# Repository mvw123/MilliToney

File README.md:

MilliToney Board 
================

Milliohmeter and tone generator
Used for measuring resistancefrom approx 1m Ohm to 1 ohm and for finding short circuits by generating a tone. 
Design files are in Eagle (free version).

CAD A - [Work In progress]
=====================

Schematic Done. 
Part values to be decided.
CAD A ordered from Elecrow. $15.00 for 10 off. 2016Jan16
PCBs arrived. 
Circuit not functioning fully. Needs the V-F circuit correcting. Also the milliohmeter is not as accurate as expected.
See issues list for details.

MVW

www.guvvy.co.uk

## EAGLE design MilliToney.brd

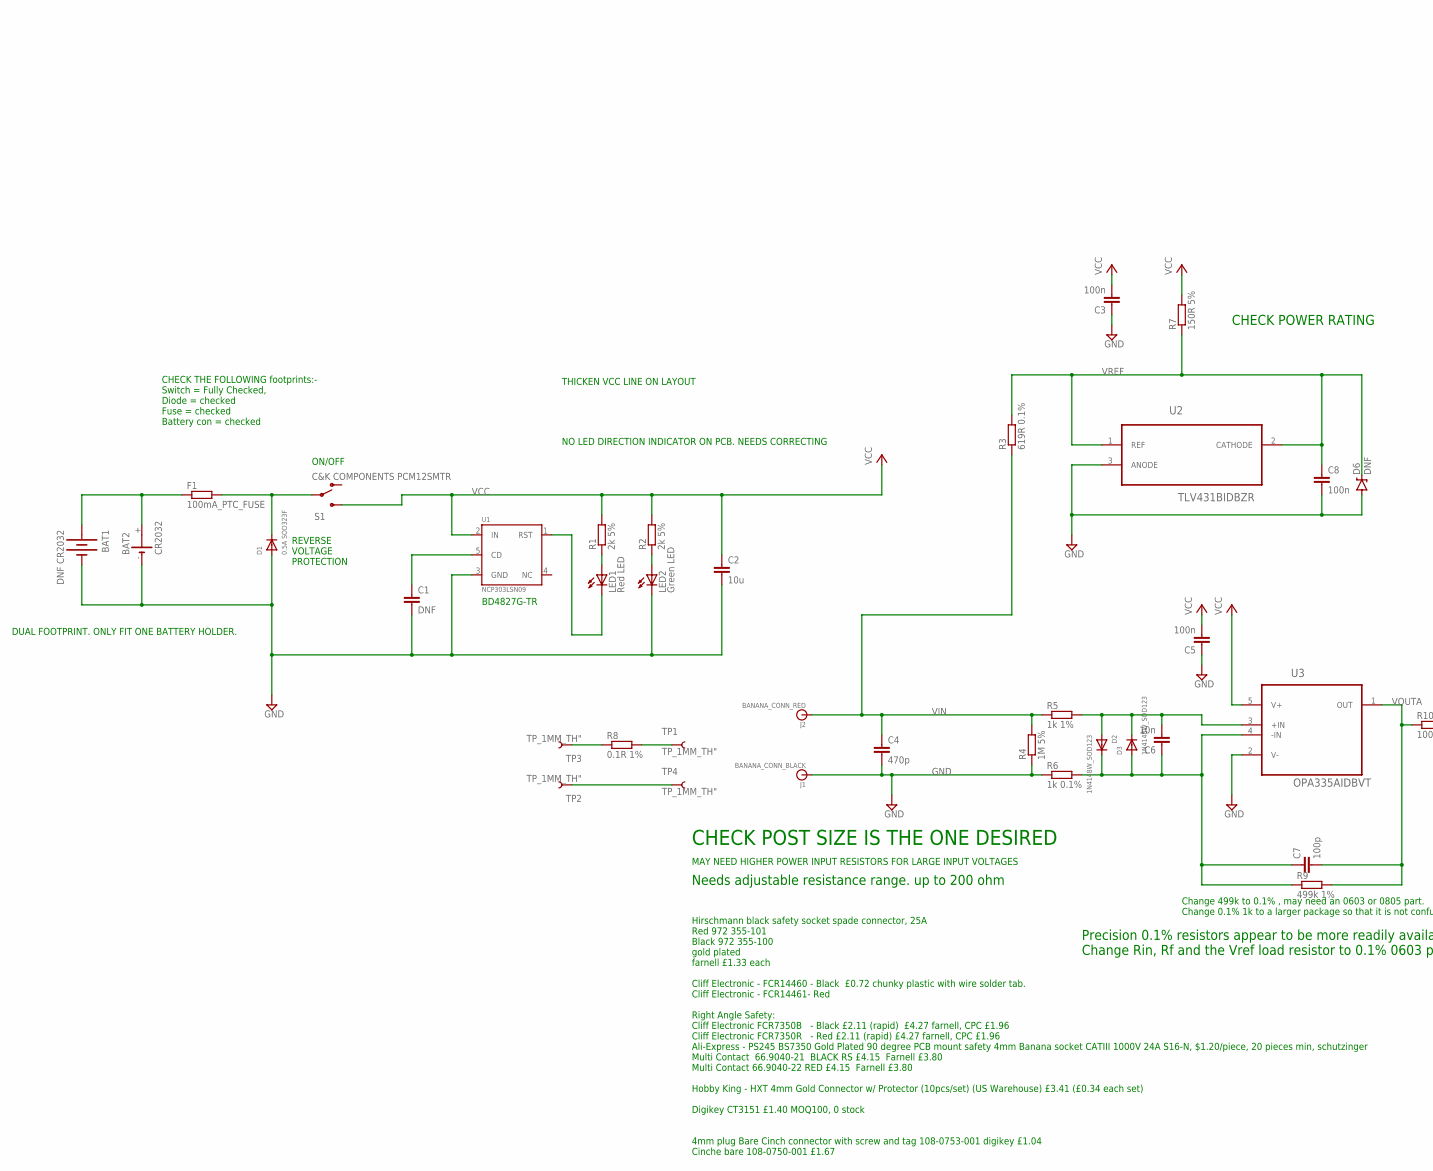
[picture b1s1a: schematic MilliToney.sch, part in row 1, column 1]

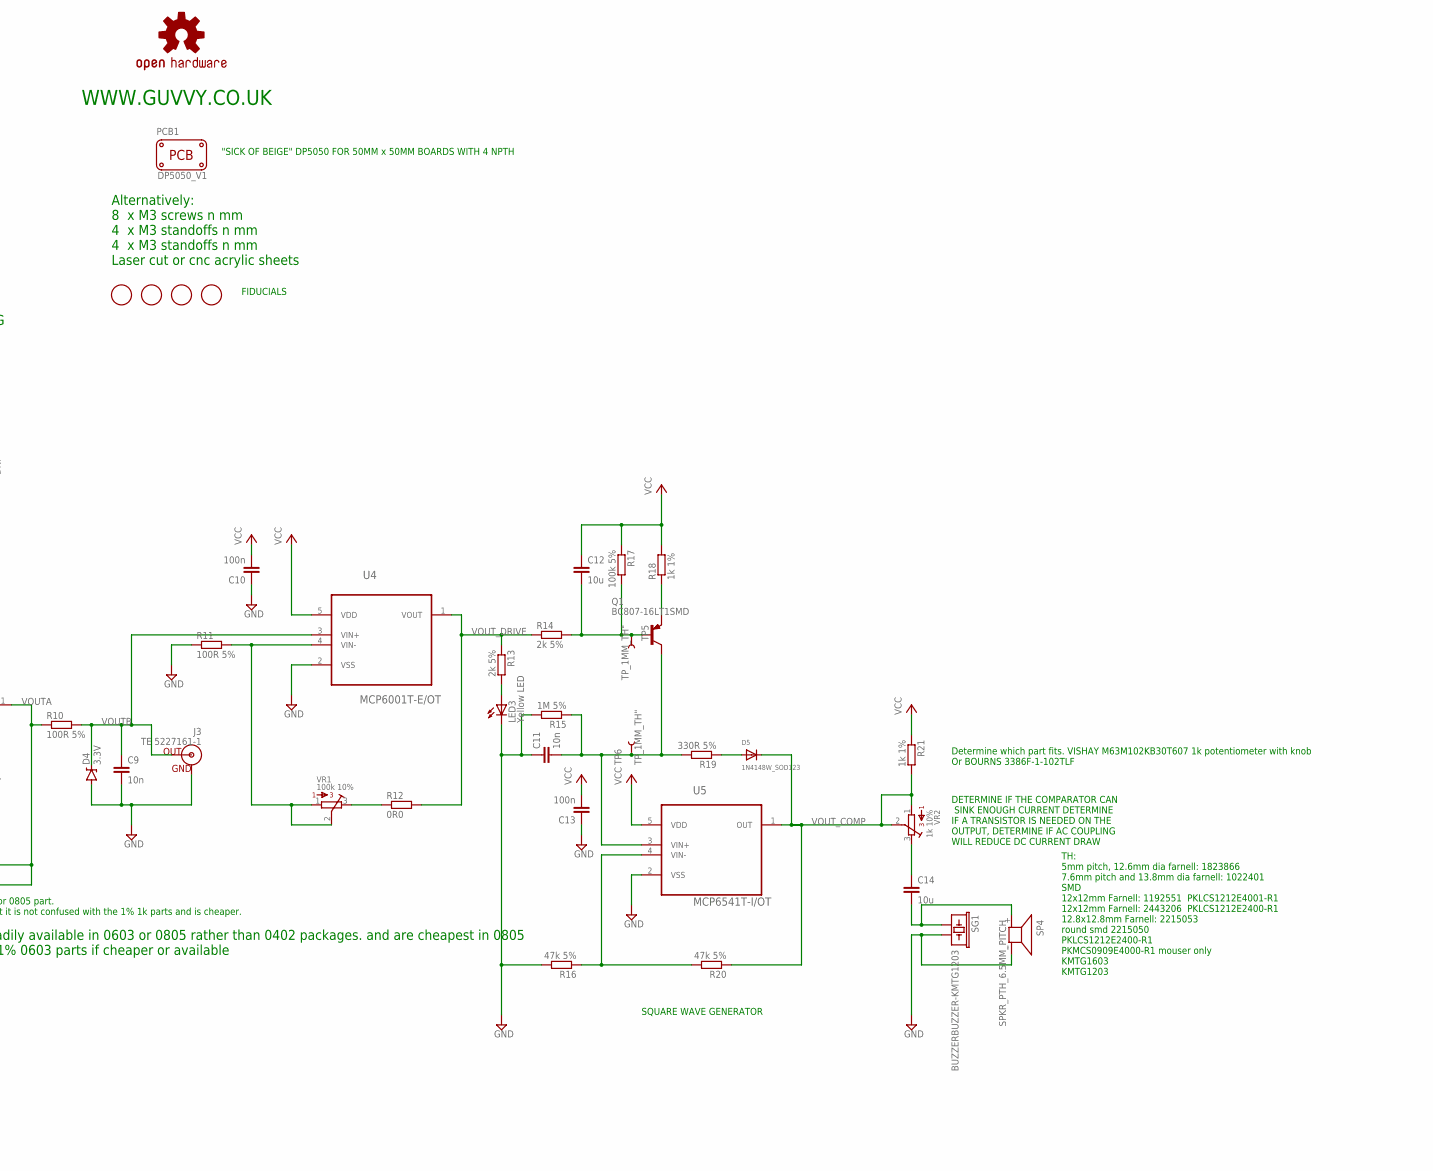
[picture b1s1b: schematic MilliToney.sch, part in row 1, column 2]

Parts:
BAT1: DNF CR2032; BATTERY_20MM_PTH_COMPACT
BAT2: CR2032; KZH20SMD; MPN SMTU 2032-LF
C1: DNF; C0402K
C2, C12: 10u; C0603; MPN GRM188R61A106ME69D
C3, C5, C8, C10, C13: 100n; C0402K; MPN MC0402X104K100CT
C4: 470p; C0402K
C6, C9, C11: 10n; C0402K
C7: 100p; C0402K
C14: 10u; C0603K; MPN GRM188R61A106ME69D
D1: 0.5A SOD323F; SOD-323F; MPN PMEG3010EJ,115
D2, D3, D5: 1N4148W_SOD123; SOD-123FL; MPN 1N4148W
D4: 3.3V; SOD-323
D6: DNF; SOD-323
F1: 100mA_PTC_FUSE; R0805; MPN MF-PSMF010X-2
FID1, FID2, FID3, FID4: FIDUCIAL; FIDUCIAL_1MM
J1: BANANA_CONN_BLACK; BANANA_CONN; MPN FCR14460
J2: BANANA_CONN_RED; BANANA_CONN; MPN FCR14461
J3: TE 5227161-1; BNC; MPN 5227161-1
LED1: Red LED; SML0603; MPN KP-1608SURCK
LED2: Green LED; SML0603; MPN KP-1608CGCK
LED3: Yellow LED; SML0603; MPN KP-1608SYCK
LOGO1: OSHW-LOGOL; OSHW-LOGO-L
PCB1: PCB_DP_SQUARE-5X5; DP5050_V1
Q1: BC807-16LT1SMD; SOT23-BEC; MPN BC807-16LT1G
R1, R2, R13, R14: 2k 5%; R0402
R3: 619R 0.1%; R0402; MPN CPF0402B619RE1
R4, R15: 1M 5%; R0402
R5, R18, R21: 1k 1%; R0402
R6: 1k 0.1%; R0402; MPN PCF0402-R-1K-B-T1.
R7: 150R 5%; R0402
R8: 0.1R 1%; R0603; MPN ERJ3RSFR10V
R9: 499k 1%; R0402; MPN ERJ3EKF4993V
R10, R11: 100R 5%; R0402
R12: 0R0; R0402
R16, R20: 47k 5%; R0402
R17: 100k 5%; R0402
R19: 330R 5%; R0402
S1: C&K COMPONENTS PCM12SMTR; SWITCH-SPST-SMD-A; MPN PCM12SMTR
SG1: BUZZERBUZZER-KMTG1203; BUZZER-KMTG1203; MPN KMTG1203
SP4: SPKR_PTH_6.5MM_PITCH; KSS1201
TP1, TP2, TP3, TP4, TP5, TP6: TP_1MM_TH"; TP_1MM_TH
U1: NCP303LSN09; SOT23-5; MPN BD4827G-TR
U2: TLV431BIDBZR; SOT95P237X112-3N; MPN TLV431BCDBZTG4
U3: OPA335AIDBVT; SOT95P280X145-5N
U4: MCP6001T-E/OT; SOT95P270X145-5N
U5: MCP6541T-I/OT; SOT95P290X145-5N
VR1: 100k 10%; 3386F; MPN 3386F-1-104TLF
VR2: 1k 10%; 3386F; MPN 3386F-1-102TLF

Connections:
GND: BAT1.2 (-), BAT2.-, C1.2, C2.2, C3.1, C4.2, C5.1, C8.2, C9.2, C10.1, C11.1, C13.1, D1.A, D4.A, D6.A, J1.P$1, J3.GND, LED2.C, LED3.C, R4.1, R6.1, R11.1, R15.2, R16.2, SG1.2, SP4.- (2), U1.3 (GND), U2.3 (ANODE), U3.2 (V-), U4.2 (VSS), U5.2 (VSS)
unnamed: BAT1.1 (+), BAT2.+, F1.1
unnamed: C14.2, SG1.1, SP4.+ (1)
unnamed: R8.1, TP3.P$1
unnamed: C6.2, D2.A, D3.C, R5.2, U3.3 (+IN)
unnamed: TP2.P$1, TP4.P$1
unnamed: D5.A, R19.1
unnamed: C6.1, C7.1, D2.C, D3.A, R6.2, R9.1, U3.4 (-IN)
unnamed: R12.1, VR1.3
unnamed: R11.2, U4.4 (VIN-), VR1.1, VR1.2
unnamed: LED1.C, U1.1 (RST)
unnamed: C12.2, Q1.B, R14.2, R17.2, TP5.P$1
unnamed: Q1.E, R18.1
unnamed: D1.C, F1.2, S1.2
unnamed: C1.1, U1.5 (CD)
unnamed: R16.1, R20.2, U5.4 (VIN-)
unnamed: C14.1, VR2.3
unnamed: LED3.A, R13.2
unnamed: C11.2, Q1.C, R15.1, R19.2, TP6.P$1, U5.3 (VIN+)
unnamed: LED1.A, R1.1
unnamed: R8.2, TP1.P$1
unnamed: LED2.A, R2.1
VCC: C2.1, C3.2, C5.2, C10.2, C12.1, C13.2, R1.2, R2.2, R7.2, R17.1, R18.2, R21.1, S1.3 (S), U1.2 (IN), U3.5 (V+), U4.5 (VDD), U5.5 (VDD)
VIN: C4.1, J2.P$1, R3.1, R4.2, R5.1
VOUTA: C7.2, R9.2, R10.1, U3.1 (OUT)
VOUTB: C9.1, D4.C, J3.S (OUT), R10.2, U4.3 (VIN+)
VOUT_COMP: D5.C, R20.1, R21.2, U5.1 (OUT), VR2.1, VR2.2
VOUT_DRIVE: R12.2, R13.1, R14.1, U4.1 (VOUT)
VREF: C8.1, D6.C, R3.2, R7.1, U2.1 (REF), U2.2 (CATHODE)

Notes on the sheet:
REVERSE VOLTAGE PROTECTION
ON/OFF
WWW.GUVVY.CO.UK
DETERMINE IF THE COMPARATOR CAN SINK ENOUGH CURRENT DETERMINE IF A TRANSISTOR IS NEEDED ON THE OUTPUT, DETERMINE IF AC COUPLING WILL REDUCE DC CURRENT DRAW
CHECK THE FOLLOWING footprints:- Switch = Fully Checked, Diode = checked Fuse = checked Battery con = checked
MAY NEED HIGHER POWER INPUT RESISTORS FOR LARGE INPUT VOLTAGES
BD4827G-TR
SQUARE WAVE GENERATOR
"SICK OF BEIGE" DP5050 FOR 50MM x 50MM BOARDS WITH 4 NPTH
FIDUCIALS
DUAL FOOTPRINT. ONLY FIT ONE BATTERY HOLDER.
CHECK POST SIZE IS THE ONE DESIRED
Hirschmann black safety socket spade connector, 25A Red 972 355-101 Black 972 355-100 gold plated farnell £1.33 each Cliff Electronic - FCR14460 - Black £0.72 chunky plastic with wire solder tab. Cliff Electronic - FCR14461- Red Right Angle Safety: Cliff Electronic FCR7350B - Black £2.11 (rapid) £4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
Needs adjustable resistance range. up to 200 ohm
TH: 5mm pitch, 12.6mm dia farnell: 1823866 7.6mm pitch and 13.8mm dia farnell: 1022401 SMD 12x12mm Farnell: 1192551 PKLCS1212E4001-R1 12x12mm Farnell: 2443206 PKLCS1212E2400-R1 12.8x12.8mm Farnell: 2215053 round smd 2215050 PKLCS1212E2400-R1 PKMCS0909E4000-R1 mouser only KMTG1603 KMTG1203
Alternatively: 8 x M3 screws n mm 4 x M3 standoffs n mm 4 x M3 standoffs n mm Laser cut or cnc acrylic sheets
Precision 0.1% resistors appear to be more readily available in 0603 or 0805 rather than 0402 packages. and are cheapest in 0805 Change Rin, Rf and the Vref load resistor to 0.1% 0603 parts if cheaper or available
CHECK POWER RATING
Determine which part fits. VISHAY M63M102KB30T607 1k potentiometer with knob Or BOURNS 3386F-1-102TLF
NO LED DIRECTION INDICATOR ON PCB. NEEDS CORRECTING
THICKEN VCC LINE ON LAYOUT
Change 499k to 0.1% , may need an 0603 or 0805 part. Change 0.1% 1k to a larger package so that it is not confused with the 1% 1k parts and is cheaper.

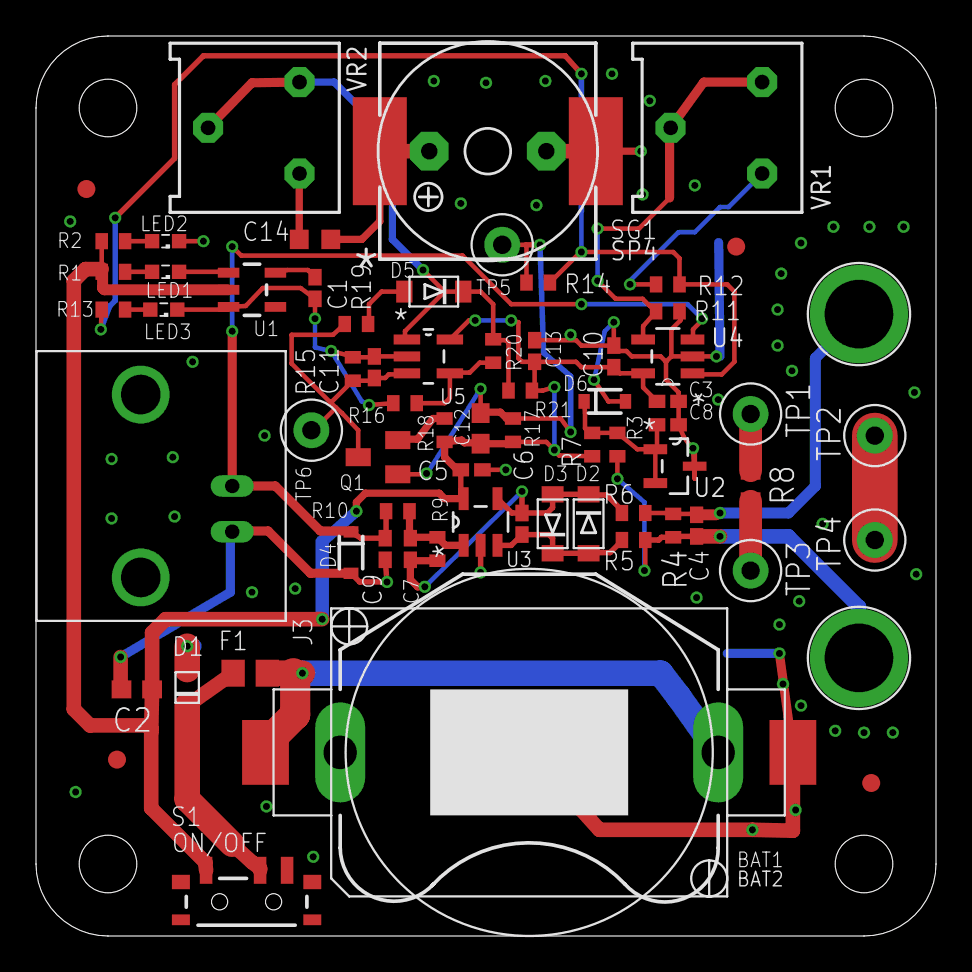
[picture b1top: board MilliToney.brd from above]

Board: 2 copper layers, 50.0 x 50.0 mm, 73 parts (1 on the bottom side), 29 nets.

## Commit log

2015-10-25 First Commit
    Rough schematic, not completed.
2016-01-10 Committing latest updates
    Committing latest updates. dual footprints buzzer and battery, updated
    other parts. added 5x5 footprint for board
2016-01-15 Minor updates
    Minor Updates
2016-01-15 CAD A Release Version
    CAD A Release Version
    Moved battery inboard requiring moving of various components
2016-01-15 Updated description
2016-01-26 minor movement on the schematic
    minor movement on the schematic
2016-02-21 Updated part values and part number
    Updated part values and part number
2016-02-28 updated layout and parts
    updated layout and parts
2017-09-25 minor updates
2018-02-12 minor update

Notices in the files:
parts and their libraries:
SparkFun-Connectors: Licensing: Creative Commons ShareAlike 4.0 International - https://creativecommons.org/licenses/by-sa/4.0
